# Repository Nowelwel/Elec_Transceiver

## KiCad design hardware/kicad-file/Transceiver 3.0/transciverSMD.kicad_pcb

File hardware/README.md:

# Dokumentasi Transceiver
Folder ini berisi semua file hardware untuk proyek **Transceiver Board**. Gunakan Software di bawah ini untuk akses file Hardware
- [KiCad](https://kicad.org/)
- [Eagle](https://www.autodesk.com/products/eagle) 

## 📃 Schematic
Berikut adalah schematic dari Transceiver Board 2.0. 

## BOM
Berikut adalah BOM board Transceiver 2.0.

|References|Quantity|Package|Value|Desc|
|:-:|:------:|:----:|:---:|:--:|
|C1|1|0805|100nF|Capacitor|
|R13, R16-R18, R21-R24|8|0805|330R|Resistor|
|R19, R20, R30, R31|4|0805|10K|Resistor|
|LED1, LED 2|2|1206| - | LED|
|IC1|1|SO14|74HCT14D|Hex inverter with Schmitt-trigger inputs|
|IC2|1|SO14|74HCT125D|Quad buffer|
|D1|1|SOT-23|SRV05-4|Diode array|
|U$1|1|TRANSCEIVER_2.0|TRANSCEIVER_2.0|Socket|

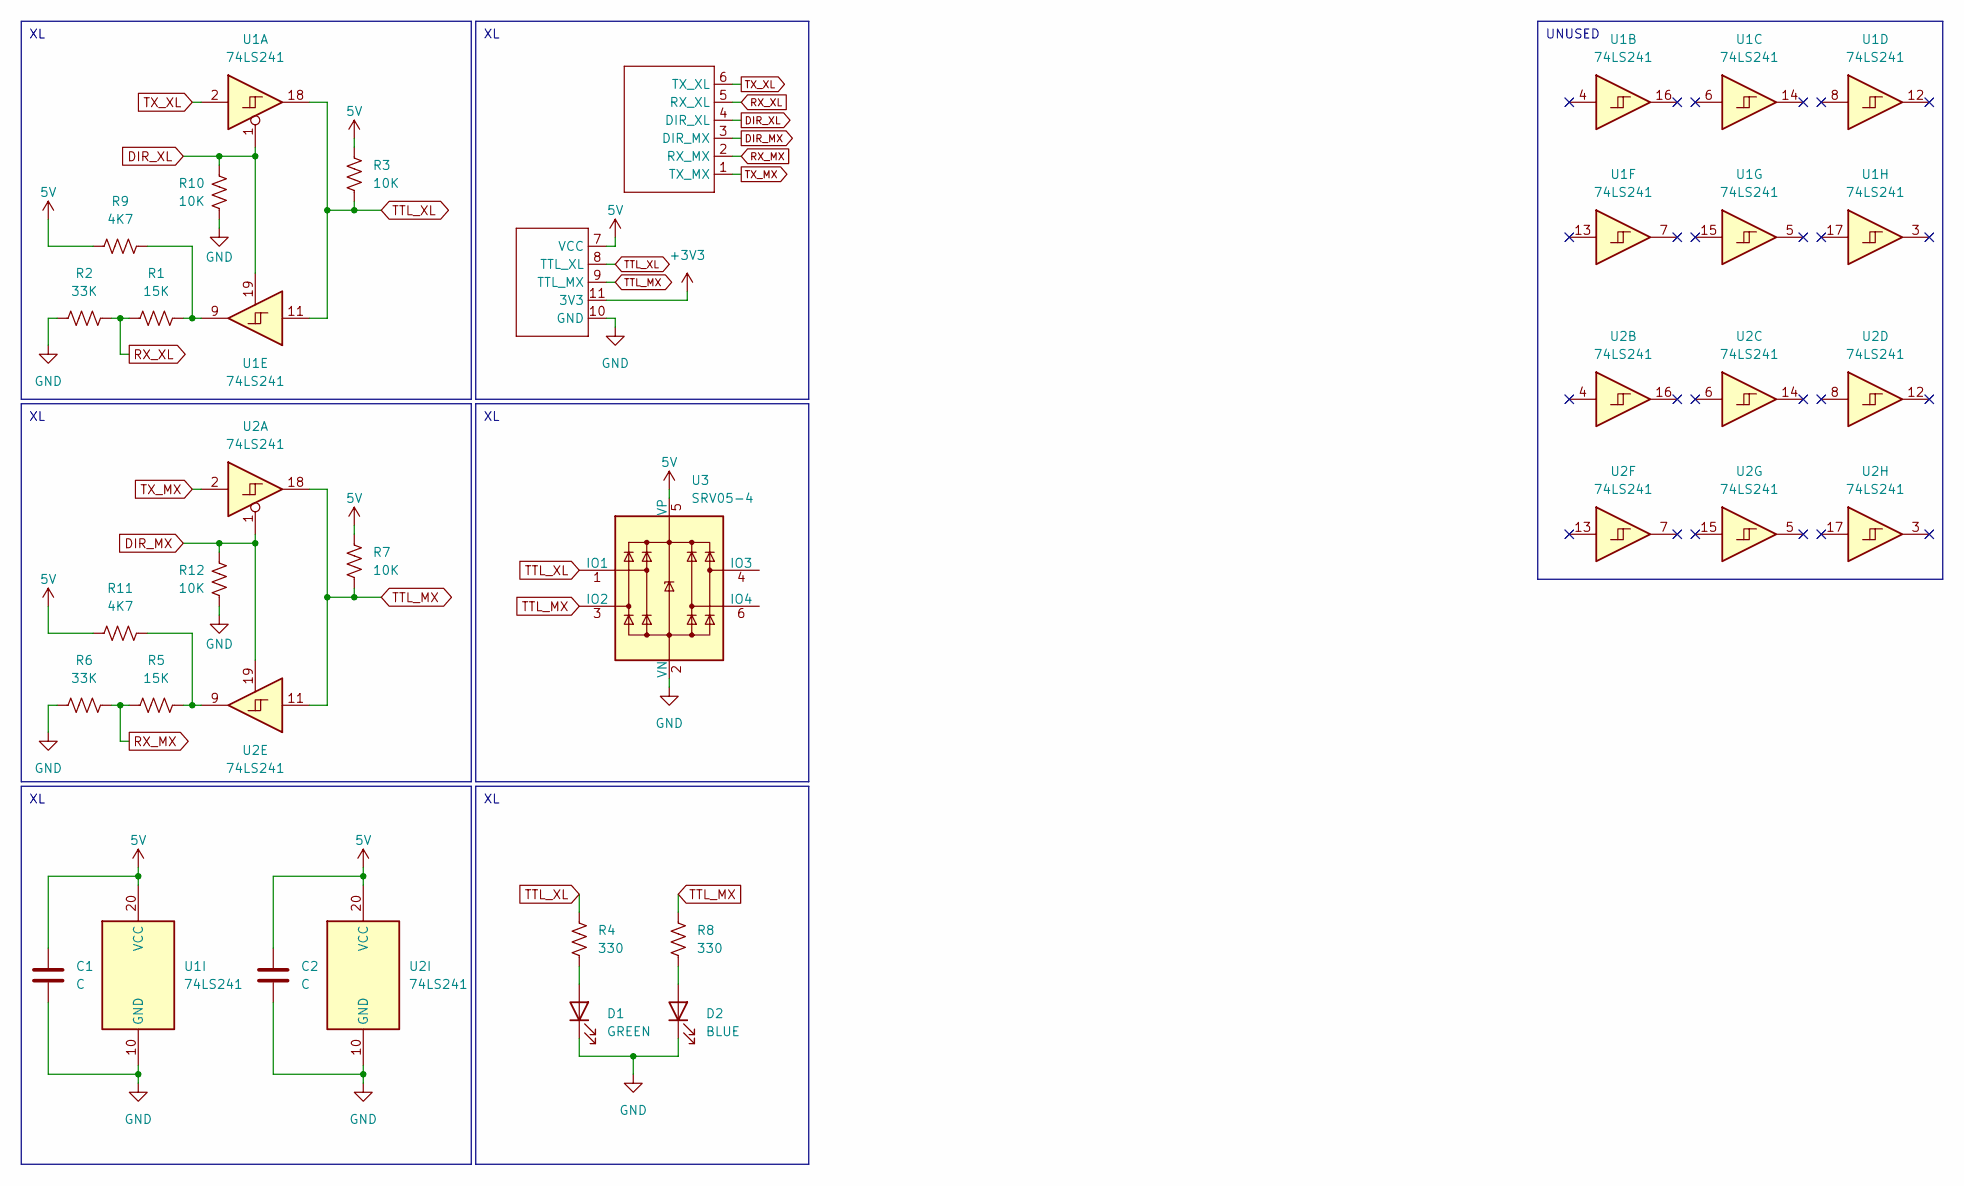
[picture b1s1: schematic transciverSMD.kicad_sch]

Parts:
C1, C2: C; C_0805_2012Metric
D1: GREEN; LED_0805_2012Metric
D2: BLUE; LED_0805_2012Metric
R1, R5: 15K; R_0805_2012Metric
R2, R6: 33K; R_0805_2012Metric
R3, R7, R10, R12: 10K; R_0805_2012Metric
R4, R8: 330; R_0805_2012Metric
R9, R11: 4K7; R_0805_2012Metric
U1, U2: 74LS241; DIP-20_W7.62mm_SMDSocket_SmallPads
U3: SRV05-4; SOT-23-6
U$1: TRANSCEIVER_2.0

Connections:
5V: C1.1, C2.1, R3.2, R7.2, R9.1, R11.1, U1.20 (VCC), U2.20 (VCC), U3.5 (VP), U$1.7 (VCC)
+3V3: U$1.11 (3V3)
DIR_MX: R12.2, U2.1, U2.19, U$1.3 (DIR_MX)
DIR_XL: R10.2, U1.1, U1.19, U$1.4 (DIR_XL)
GND: C1.2, C2.2, D1.1 (K), D2.1 (K), R2.1, R6.1, R10.1, R12.1, U1.10 (GND), U2.10 (GND), U3.2 (VN), U$1.10 (GND)
unnamed: D1.2 (A), R4.1
unnamed: D2.2 (A), R8.1
unnamed: R1.2, R9.2, U1.9
unnamed: R5.2, R11.2, U2.9
RX_MX: R5.1, R6.2, U$1.2 (RX_MX)
RX_XL: R1.1, R2.2, U$1.5 (RX_XL)
TTL_MX: R7.1, R8.2, U2.11, U2.18, U3.3 (IO2), U$1.9 (TTL_MX)
TTL_XL: R3.1, R4.2, U1.11, U1.18, U3.1 (IO1), U$1.8 (TTL_XL)
TX_MX: U2.2, U$1.1 (TX_MX)
TX_XL: U1.2, U$1.6 (TX_XL)

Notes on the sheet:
UNUSED

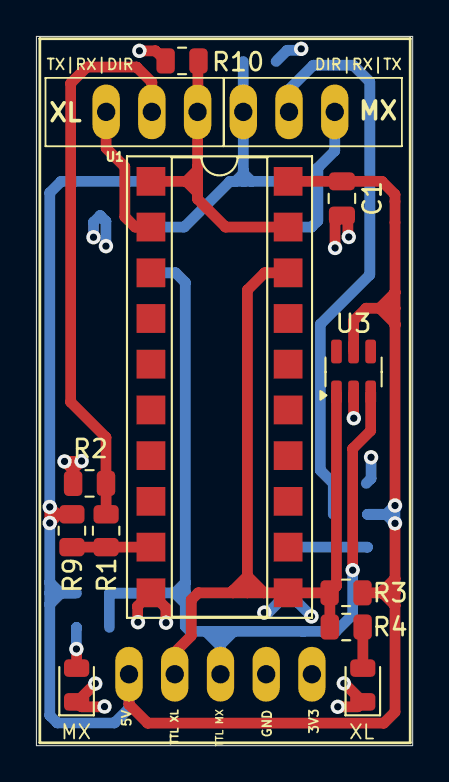
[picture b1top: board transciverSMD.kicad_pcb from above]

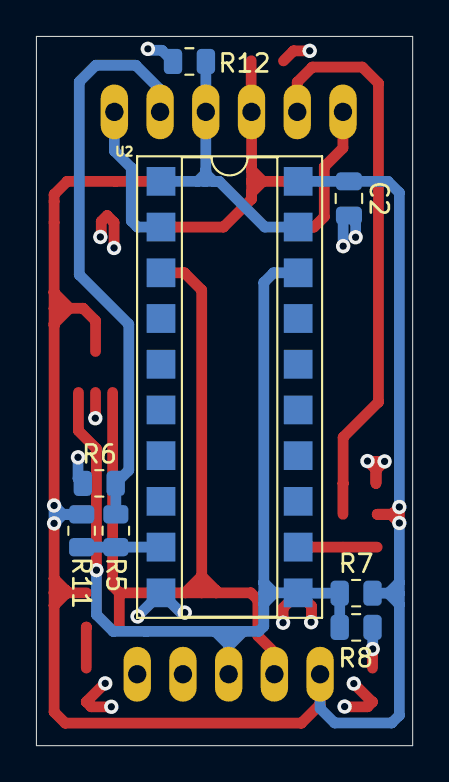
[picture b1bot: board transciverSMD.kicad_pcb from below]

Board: 4 copper layers, 20.9 x 39.4 mm, 20 parts (8 on the bottom side), 14 nets.

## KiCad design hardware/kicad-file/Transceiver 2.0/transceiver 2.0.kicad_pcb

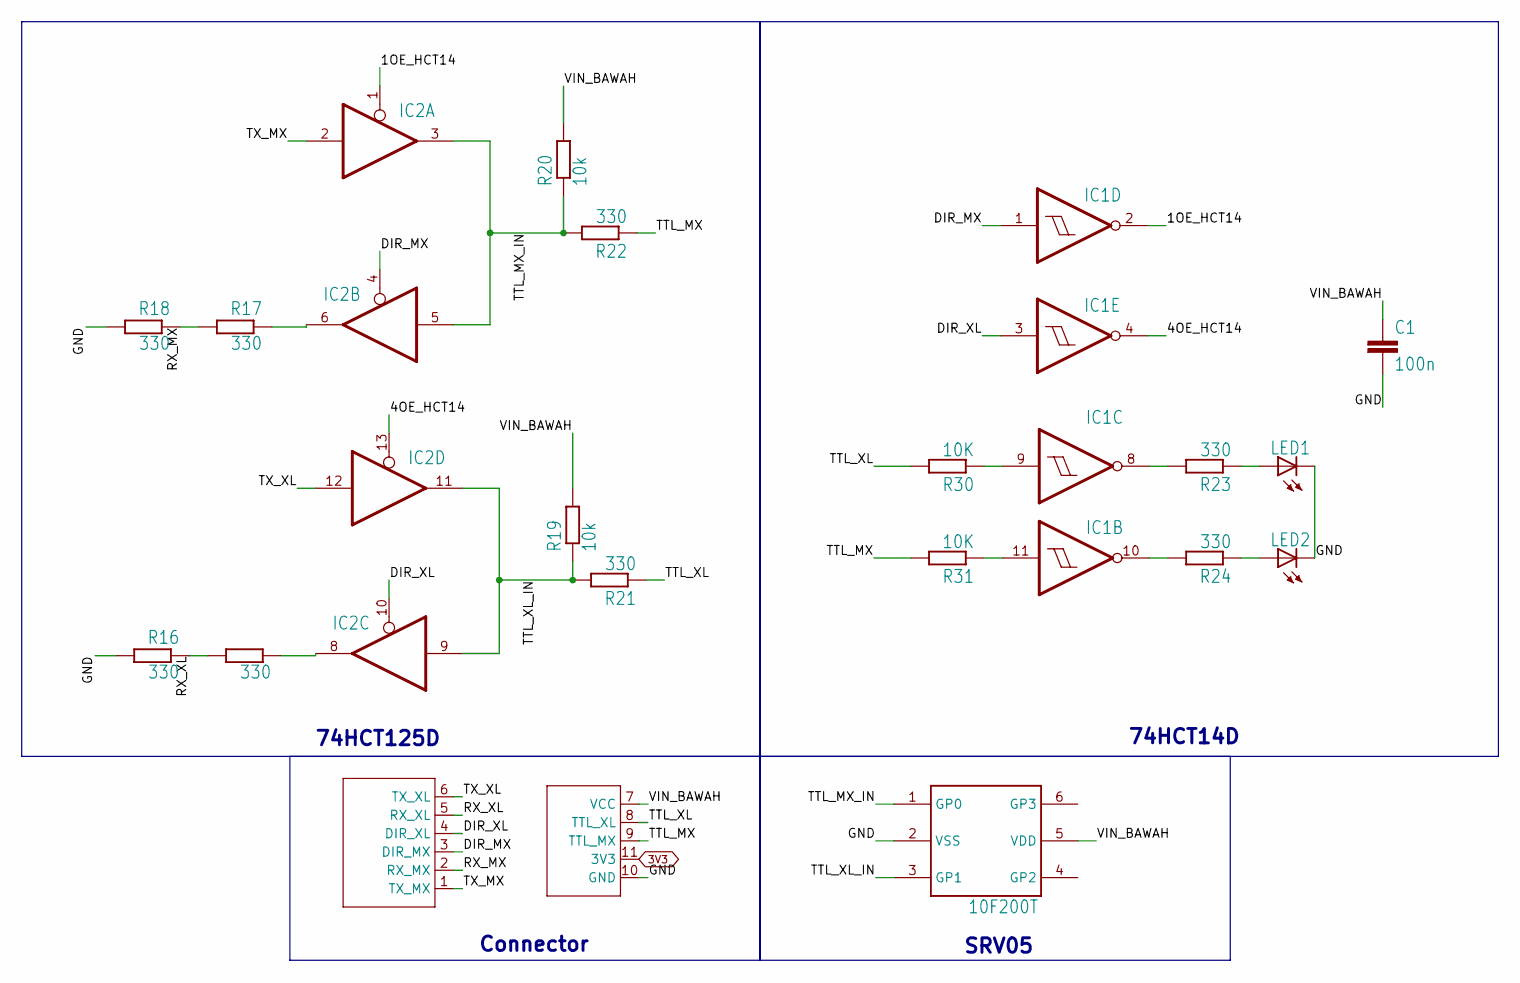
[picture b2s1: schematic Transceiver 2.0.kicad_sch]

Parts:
C1: 100n; C0805
IC1: 7414D; SO14
IC2: 74125D; SO14
LED1, LED2: LEDCHIPLED_1206; CHIPLED_1206
R13, R16, R17, R18, R21, R22, R23, R24: 330; R0805
R19, R20: 10k; R0805
R30, R31: 10K; R0805
SRV05-4: 10F200T; SOT23-6
U$1: TRANSCEIVER_2.0

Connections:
1OE_HCT14: IC1.2 (O), IC2.1 (OE)
3V3: U$1.11 (3V3)
4OE_HCT14: IC1.4 (O), IC2.13 (OE)
DIR_MX: IC1.1 (I), IC2.4 (OE), U$1.3 (DIR_MX)
DIR_XL: IC1.3 (I), IC2.10 (OE), U$1.4 (DIR_XL)
GND: C1.2, IC1.7 (GND), IC2.7 (GND), LED1.C, LED2.C, R16.2, R18.2, SRV05-4.2 (VSS), U$1.10 (GND)
unnamed: IC1.10 (O), R24.2
unnamed: LED2.A, R24.1
unnamed: IC1.8 (O), R23.2
unnamed: LED1.A, R23.1
unnamed: IC1.9 (I), R30.1
unnamed: IC1.11 (I), R31.1
unnamed: IC2.6 (O), R17.1
unnamed: IC2.8 (O), R13.1
RX_MX: R17.2, R18.1, U$1.2 (RX_MX)
RX_XL: R13.2, R16.1, U$1.5 (RX_XL)
TTL_MX: R22.1, R31.2, U$1.9 (TTL_MX)
TTL_MX_IN: IC2.3 (O), IC2.5 (I), R20.1, R22.2, SRV05-4.1 (GP0)
TTL_XL: R21.1, R30.2, U$1.8 (TTL_XL)
TTL_XL_IN: IC2.9 (I), IC2.11 (O), R19.1, R21.2, SRV05-4.3 (GP1)
TX_MX: IC2.2 (I), U$1.1 (TX_MX)
TX_XL: IC2.12 (I), U$1.6 (TX_XL)
VIN_BAWAH: C1.1, IC1.14 (VIN_BAWAH), IC2.14 (VIN_BAWAH), R19.2, R20.2, SRV05-4.5 (VDD), U$1.7 (VCC)

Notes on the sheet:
Connector
74HCT14D
SRV05
74HCT125D

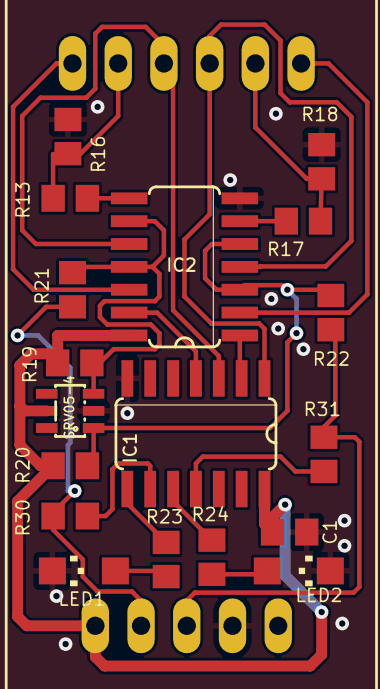
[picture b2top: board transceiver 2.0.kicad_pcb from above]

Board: 2 copper layers, 19 parts (0 on the bottom side), 22 nets.

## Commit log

2025-07-26 add .gitkeep
2025-07-26 add design-files
2025-07-26 add exports
2025-07-26 add README for hardware
2025-07-26 add.gitkeep
2025-07-26 add Transceiver 2.0 image
2025-07-26 schematic 2.0
2025-07-26 Rename Transceiver 2.0 Schematic.jpg to schematic.jpg
2025-07-26 Rename Transceiver 1.0 to p
2025-07-26 Create p
2025-07-26 add Transceiver 1.0 sch
2025-07-26 Rename Transifer_HCT_panut.sch to Transceiver 1.0 sch
2025-07-26 add Transceiver 1.0 brd
2025-07-26 Rename Transifer_HCT_panut.brd to Transceiver 1.0 brd.brd
2025-07-26 Rename Transceiver 1.0 brd.brd to Transceiver 1.0 board.brd
2025-07-26 add transceiver 1.o sch
2025-07-26 Rename Transifer_HCT_panut.sch to Transceiver 1.0 .sch
2025-07-26 Rename Transceiver 1.0 .sch to Transceiver 1.0.sch
2025-07-26 Rename Transceiver 1.0 board.brd to Transceiver 1.0.brd
2025-07-26 add transceiver 2.0 pro
2025-07-26 add transceiver 2.0 sch
2025-07-26 add transceiver 2.0 brd
2025-07-26 Rename transceiver 2.0.kicad_pro to Transceiver 2.0.kicad_pro
2025-07-26 add transceiver 3.0 files
2025-07-26 add transceiver 3.0 board
2025-07-26 Rename transciverSMD.kicad_pro to Transceiver 3.0.kicad_pro
2025-07-27 add CHANGELOG.md
2025-07-27 add transceiver 2.0 html
2025-07-27 add transceiver 2.0 bom image
